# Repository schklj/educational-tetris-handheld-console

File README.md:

# educational-tetris-handheld-console
a project for schools to teach about electornics and programming

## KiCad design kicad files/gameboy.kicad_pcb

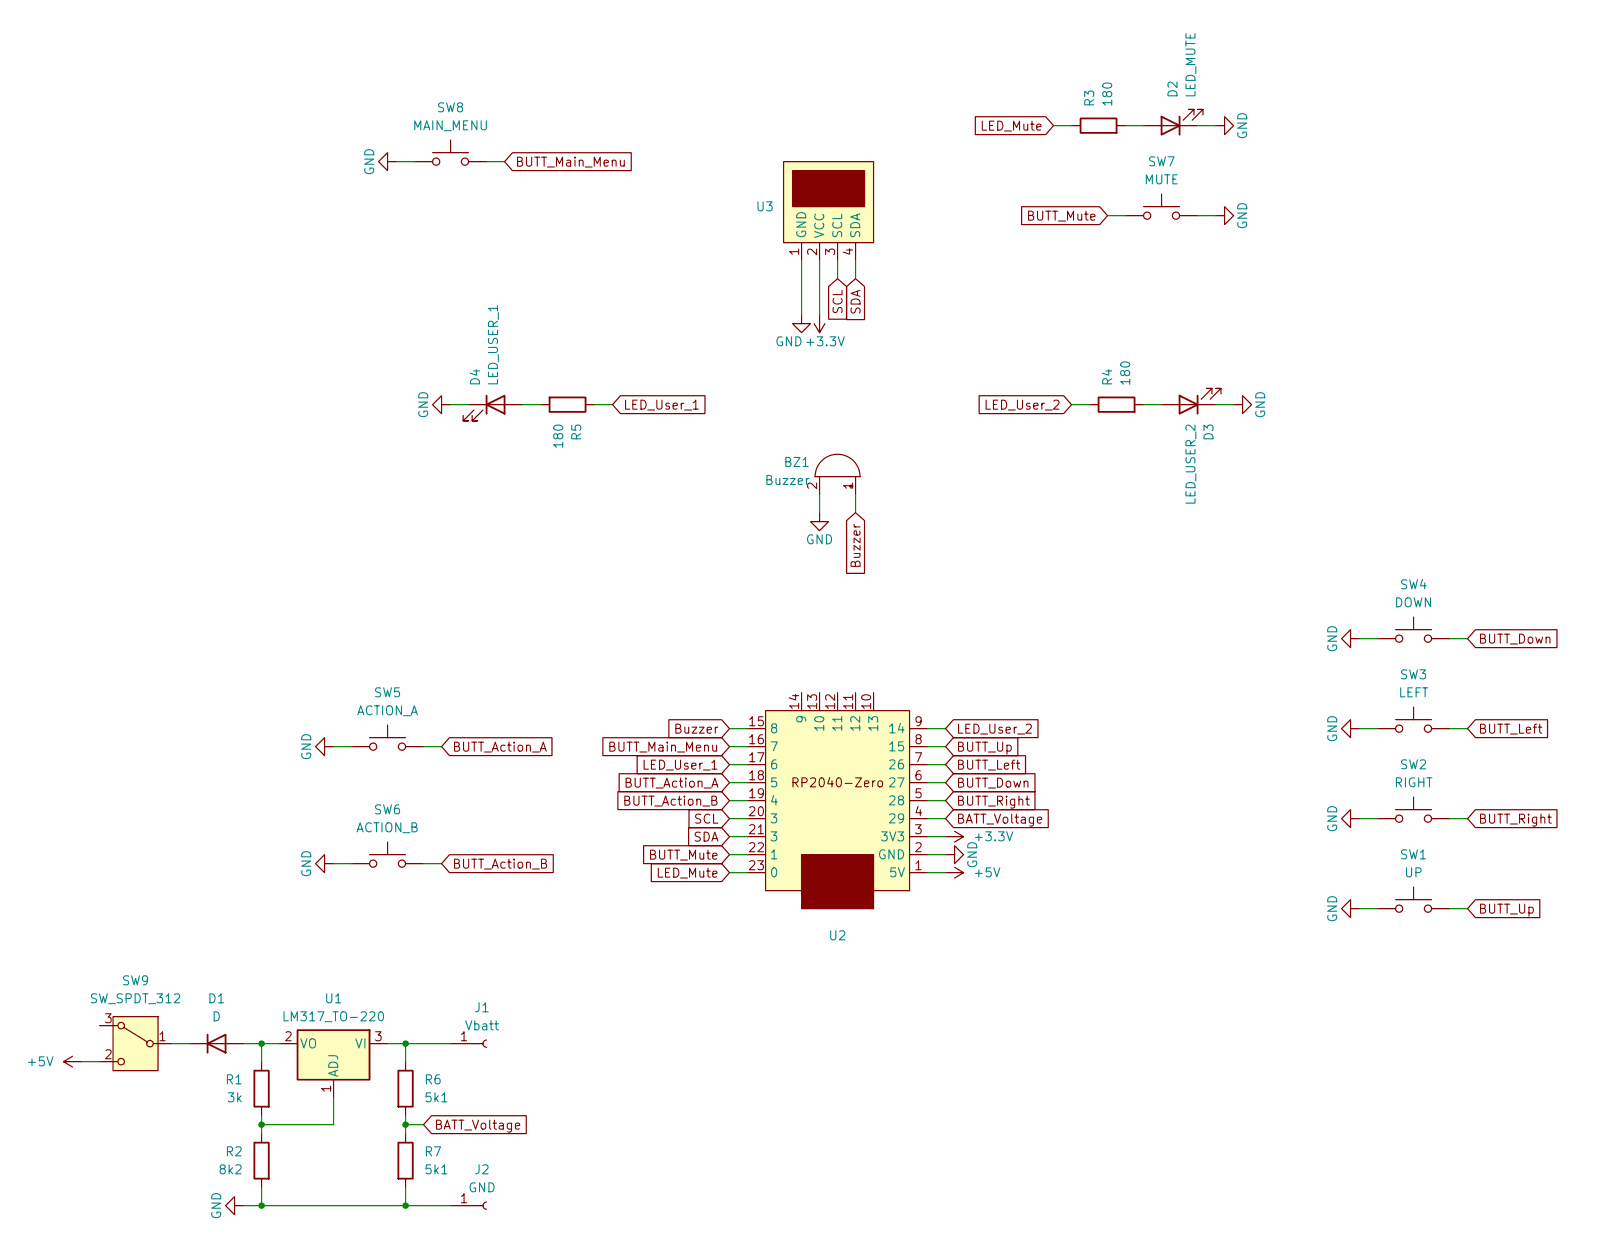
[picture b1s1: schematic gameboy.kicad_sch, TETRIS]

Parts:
BZ1: Buzzer; Buzzer_D14mm_H7mm_P10mm
D1: D; D_A-405_P10.16mm_Horizontal
D2: LED_MUTE; LED_D5.0mm
D3: LED_USER_2; LED_D5.0mm
D4: LED_USER_1; LED_D5.0mm
J1: Vbatt; TestPoint_THTPad_2.0x2.0mm_Drill1.0mm
J2: GND; TestPoint_THTPad_2.0x2.0mm_Drill1.0mm
R1: 3k; R_Axial_DIN0207_L6.3mm_D2.5mm_P7.62mm_Horizontal
R2: 8k2; R_Axial_DIN0207_L6.3mm_D2.5mm_P7.62mm_Horizontal
R3, R4, R5: 180; R_Axial_DIN0207_L6.3mm_D2.5mm_P7.62mm_Horizontal
R6, R7: 5k1; R_Axial_DIN0207_L6.3mm_D2.5mm_P7.62mm_Horizontal
SW1: UP; SW_PUSH_6mm
SW2: RIGHT; SW_PUSH_6mm
SW3: LEFT; SW_PUSH_6mm
SW4: DOWN; SW_PUSH_6mm
SW5: ACTION_A; SW_PUSH_6mm
SW6: ACTION_B; SW_PUSH_6mm
SW7: MUTE; SW_PUSH_6mm
SW8: MAIN_MENU; SW_PUSH_6mm
SW9: SW_SPDT_312; PinHeader_1x03_P2.54mm_Vertical
U1: LM317_TO-220; TO-220-3_Vertical
U2: PR2040-Zero
U3: PinHeader_1x04_P2.54mm_Vertical

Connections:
+3.3V: U2.3 (3V3), U3.2 (VCC)
+5V: SW9.2 (C), U2.1 (5V)
BATT_Voltage: R6.2, R7.1, U2.4 (29)
BUTT_Action_A: SW5.1, U2.18 (5)
BUTT_Action_B: SW6.1, U2.19 (4)
BUTT_Down: SW4.1, U2.6 (27)
BUTT_Left: SW3.1, U2.7 (26)
BUTT_Main_Menu: SW8.1, U2.16 (7)
BUTT_Mute: SW7.1, U2.22 (1)
BUTT_Right: SW2.1, U2.5 (28)
BUTT_Up: SW1.1, U2.8 (15)
Buzzer: BZ1.1 (+), U2.15 (8)
GND: BZ1.2 (-), D2.1 (K), D3.1 (K), D4.1 (K), J2.1, R2.2, R7.2, SW1.2, SW2.2, SW3.2, SW4.2, SW5.2, SW6.2, SW7.2, SW8.2, U2.2 (GND), U3.1 (GND)
LED_Mute: R3.1, U2.23 (0)
LED_User_1: R5.1, U2.17 (6)
LED_User_2: R4.1, U2.9 (14)
unnamed: D1.2 (A), R1.1, U1.2 (VO)
unnamed: D1.1 (K), SW9.1 (B)
unnamed: D2.2 (A), R3.2
unnamed: D3.2 (A), R4.2
unnamed: D4.2 (A), R5.2
unnamed: J1.1, R6.1, U1.3 (VI)
unnamed: R1.2, R2.1, U1.1 (ADJ)
SCL: U2.20 (3), U3.3 (SCL)
SDA: U2.21 (3), U3.4 (SDA)

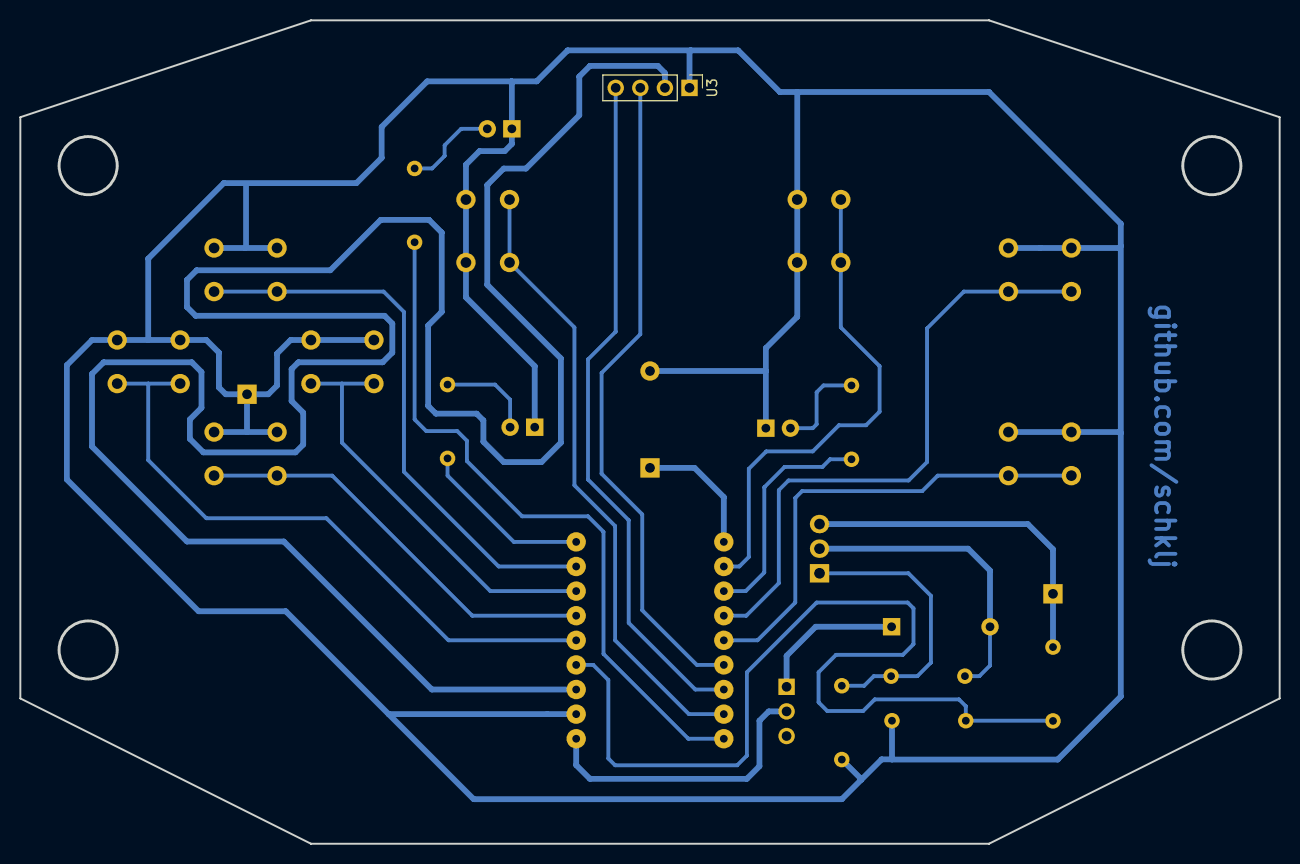
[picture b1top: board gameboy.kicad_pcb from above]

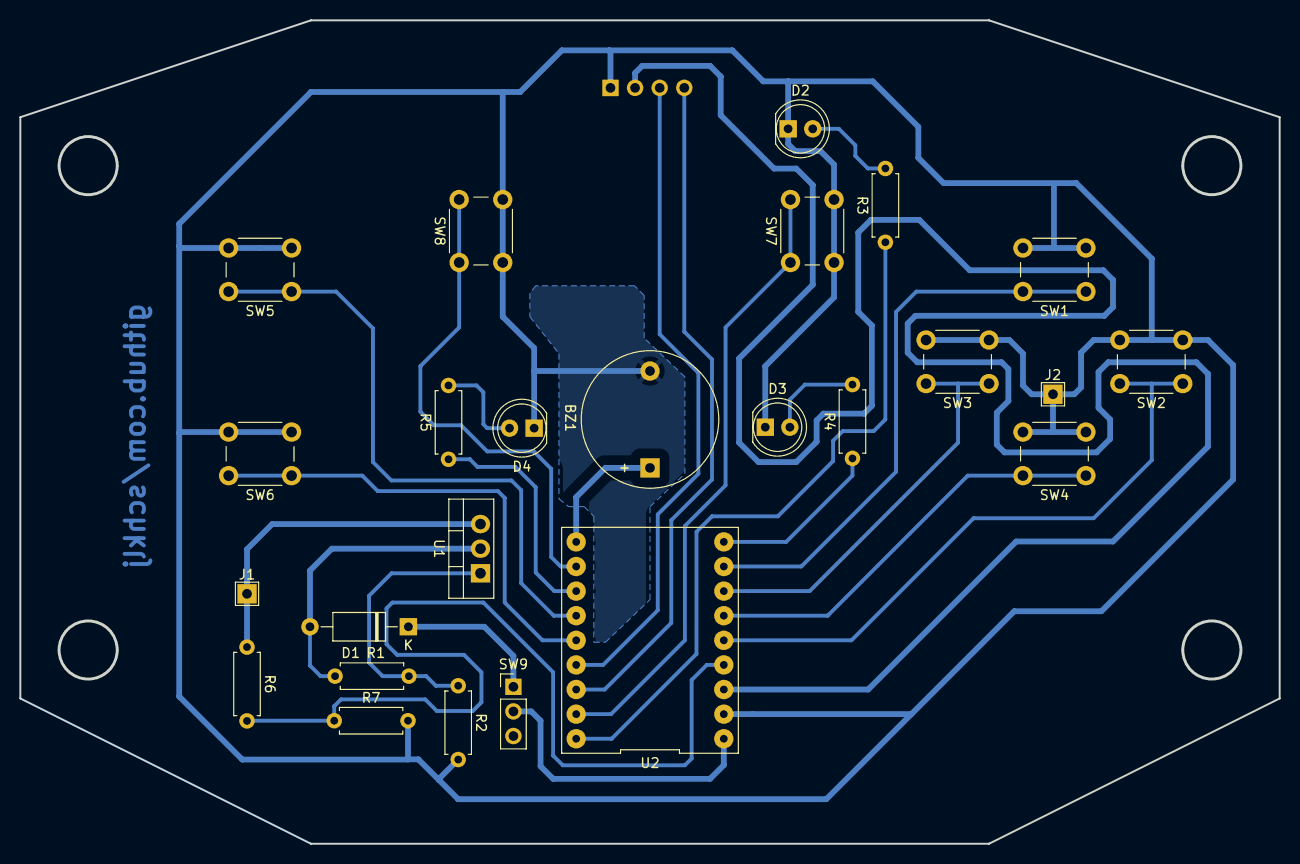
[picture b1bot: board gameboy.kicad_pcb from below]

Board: 2 copper layers, 129.9 x 84.9 mm, 26 parts (25 on the bottom side), 25 nets.

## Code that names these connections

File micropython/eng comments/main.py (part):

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is_menu = False

# definitions of LED(output) objects
led_mute = Pin(0, Pin.OUT)
led_user_1 = Pin(14, Pin.OUT)
led_user_2 = Pin(6, Pin.OUT)

# definitions of ADC object
# reading actual battery voltage doesn't work properly with currect schematic
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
